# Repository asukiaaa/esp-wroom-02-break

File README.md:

# esp-wroom-02-break
A kicad project for esp-wroom-02

# License
MIT

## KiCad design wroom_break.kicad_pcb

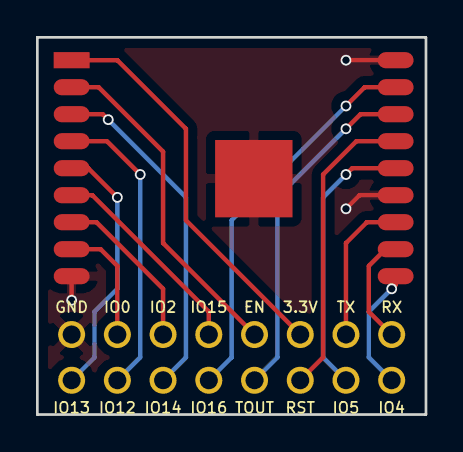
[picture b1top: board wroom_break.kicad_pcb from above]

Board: 2 copper layers, 21.6 x 21.0 mm, 3 parts (0 on the bottom side), 16 nets.

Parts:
J1, J2: HEADER_8; Pin_Header_Straight_1x08_small
U1: ESP-13-WROOM-02

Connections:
GND: J1.8, U1.9, U1.13, U1.18, U1.PAD
unnamed: J1.1, U1.11
unnamed: J1.2, U1.12
unnamed: J1.3, U1.1
unnamed: J1.4, U1.2
unnamed: J1.5, U1.6
unnamed: J1.6, U1.7
unnamed: J1.7, U1.8
unnamed: J2.1, U1.10
unnamed: J2.2, U1.14
unnamed: J2.3, U1.15
unnamed: J2.4, U1.16
unnamed: J2.5, U1.17
unnamed: J2.6, U1.3
unnamed: J2.7, U1.4
unnamed: J2.8, U1.5

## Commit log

2016-12-29 Add opensource hardware logo
2016-12-29 Change board name and vias position
2016-12-30 Add readme
2016-12-30 Remove edges from PCB
2016-12-31 Add image
2016-12-31 Add schema pdf
